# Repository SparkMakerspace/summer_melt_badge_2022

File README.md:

# Summer Melt Soldering Badge

 This badge was designed for the 2022 Summer Melt at Spark Makerspace.

 It's a *relatively* basic soldering project that results in a WiFi-enabled ice cream cone-shaped blinky pin.

## Assembly instructions:
*Coming soon...*

## Code
*Coming soon...*

## Bill of Materials (BOM)
* WeMos D1 Mini ESP8266 module (1)
* SS12D07VG4 switch (1)
* Keystone 2468 Battery Holder (1)
* DS18B20 Temperature sensor (1)
* 4.7 kOhm Resistor (THT) (1)

## Power
The badge can be powered from either two (2) AAA batteries **OR** via a USB cable connected to the ESP8266 module. Do not connect a USB cable while there are batteries in the device.

## Other
The badge also features a slot for a lanyard (not necessarily included) and a set of connector pins for [SAO](https://hackaday.io/project/175182-simple-add-ons-sao) badge add-ons often seen on Hackaday.

Interested in this kind of stuff and live in CT/RI? [Stop by our weekly Electronics & Technology Meetup on a Thursday Night!](https://electronicsnight.com).

[Spark Makerspace is a community workshop and learning center in beautiful, downtown New London, Connecticut](https://sparkmakerspace.org).

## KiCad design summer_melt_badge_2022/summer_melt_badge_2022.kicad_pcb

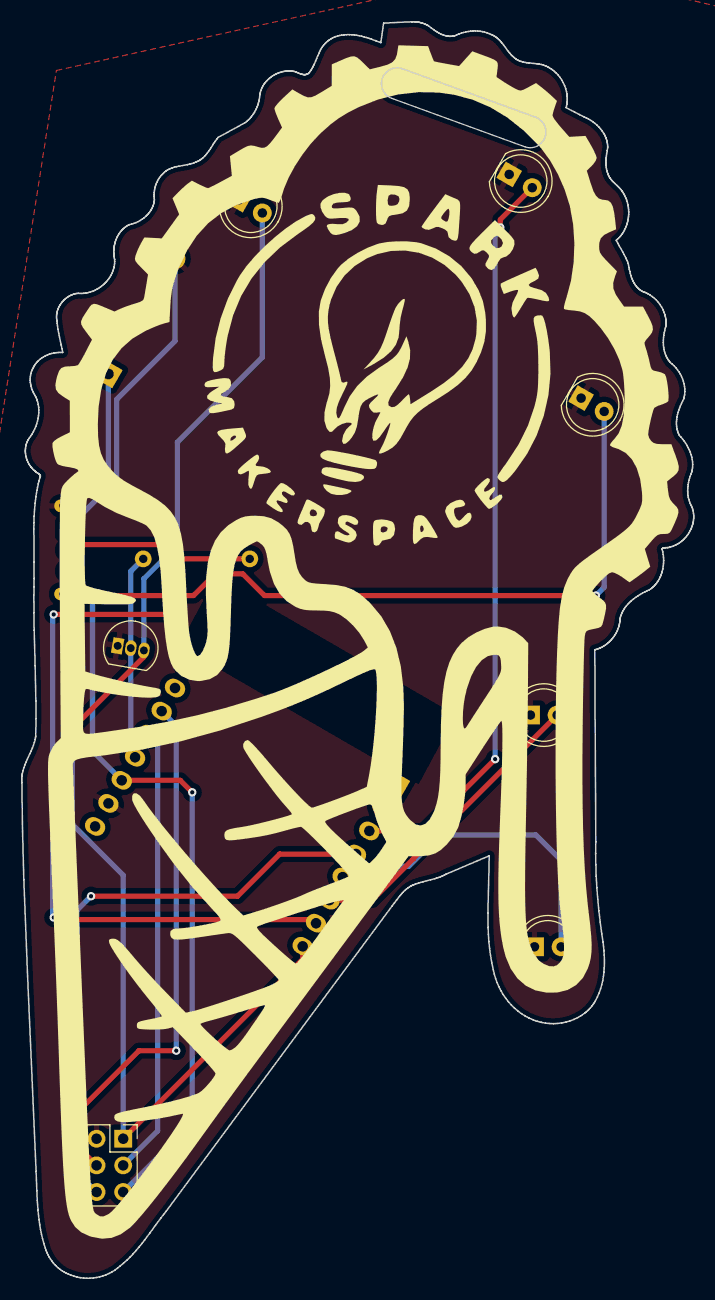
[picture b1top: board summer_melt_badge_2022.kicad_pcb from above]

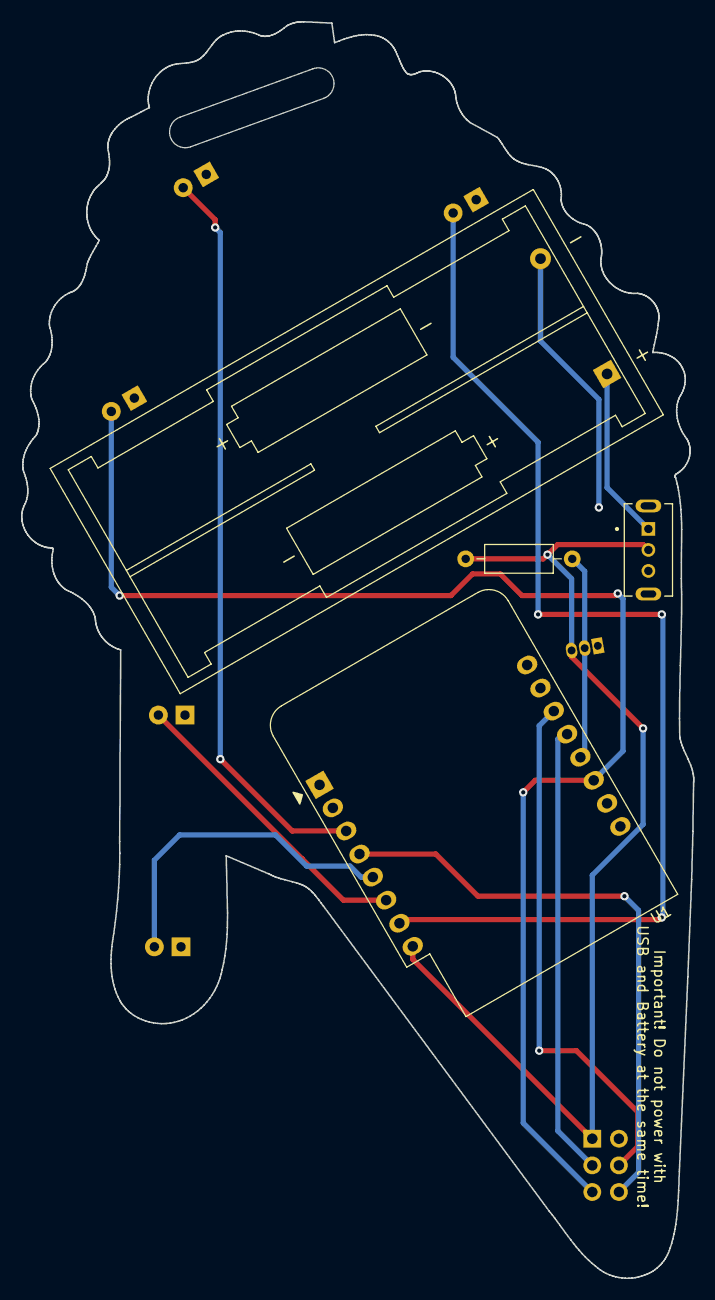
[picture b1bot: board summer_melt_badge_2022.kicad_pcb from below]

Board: 2 copper layers, 64.1 x 119.8 mm, 12 parts (4 on the bottom side), 12 nets.

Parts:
BT1: Battery; BatteryHolder_Keystone_2468_2xAAA
D1, D2, D3, D4, D5: LED; LED_D5.0mm
H1: MountingHole; lanyard_slot
J1: Conn_02x03_Odd_Even; PinSocket_2x03_P2.54mm_Vertical
R1: 4.7k; R_Axial_DIN0207_L6.3mm_D2.5mm_P10.16mm_Horizontal
S1: SS12D07VG4; SW_SS12D07VG4
U1: WeMos_D1_mini; WEMOS_D1_mini_light
U2: DS18B20; TO-92_Inline

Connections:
+3V0: J1.1, R1.1, S1.2, U1.8 (3V3), U2.3 (VDD)
+BATT: BT1.1 (+), S1.1
DQ: R1.2, U1.12 (D3), U2.2 (DQ)
GND: BT1.2 (-), D1.1 (K), D2.1 (K), D3.1 (K), D4.1 (K), D5.1 (K), J1.2, S1.S1 (SHIELD), U1.10 (GND), U2.1 (GND)
GPIO0: D2.2 (A), J1.5, U1.11 (D4)
GPIO1: J1.6, U1.4 (SCK/D5)
unnamed: D1.2 (A), U1.3 (D0)
unnamed: D3.2 (A), U1.5 (MISO/D6)
unnamed: D4.2 (A), U1.6 (MOSI/D7)
unnamed: D5.2 (A), U1.7 (CS/D8)
SCL: J1.4, U1.14 (SCL/D1)
SDA: J1.3, U1.13 (SDA/D2)

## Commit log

2022-08-14 add graphics to kicad project
2022-08-16 draft schematic for review.
2022-08-22 I made some changes to the schematic
2022-08-22 footprint assignment, placement started
2022-08-25 draft placement complete.
2022-08-27 final draft placement
2022-08-27 Minor edits during final placement review
2022-08-27 draft traces
2022-08-27 routed board review complete
2022-09-01 add readme and set up to output gerbers.
2022-09-01 move readme up one level
2022-09-01 reorganize files
